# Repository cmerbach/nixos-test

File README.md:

# NixOS

## Quick and dirty setup guide for testing

### Download and run a vm

```sh
# create a tmp folder
mkdir -p tmp

# download the current version of nixos
test ! -f tmp/nixos.iso && wget https://channels.nixos.org/nixos-25.05/latest-nixos-minimal-x86_64-linux.iso -O tmp/nixos.iso || echo "Nothing todo!"

# create the device for install the os
test ! -f tmp/nixos.img && qemu-img create -f raw tmp/nixos.img 100G || echo "Nothing todo!"
```

### Run the vm

> [!NOTE]
> **cpu <CPU> :** Specify a processor architecture to emulate. To see a list of supported architectures, run: `qemu-system-x86_64 -cpu` <br>
> **cpu host :** (Recommended) Emulate the host processor <br>
> **smp <NUMBER> :** Specify the number of cores the guest is permitted to use. The number can be higher than the available cores on the host system. Use `-smp $(nproc)` to use all currently available cores

```sh
# ---( Option A)--- #
# run the boot command with gui
qemu-system-x86_64 -enable-kvm -hda tmp/nixos.img -smp 8 -m 16G -nic user,hostfwd=tcp::8888-:22 -cdrom tmp/nixos.iso -boot d

#---( set a password to root in the vm )--- #
#~$ passwd
```

```sh
# ---( Option B)--- #
# run the boot command just in plain terminal
qemu-system-x86_64 -enable-kvm -hda tmp/nixos.img -smp 8 -m 16G -nic user,hostfwd=tcp::8888-:22 -cdrom tmp/nixos.iso -boot d -nographic -serial mon:stdio

#---( set a password to root in the vm )--- #
#~$ passwd
```

### Login to vm

```sh
ssh-keygen -f "/home/user/.ssh/known_hosts" -R "[127.0.0.1]:8888" && \
sshpass -p '123' \
ssh -o StrictHostKeyChecking=no -o PreferredAuthentications=password nixos@127.0.0.1 -p 8888
```

### Run install

> [!IMPORTANT]  
> The default repo you are using is: **nixos**

> [!CAUTION]
> To run disko needs **2GB** of additional space

#### install by hand

```sh
# set env variables
export ACCOUNT=
export BRANCH=
# run the install 
nix --experimental-features "nix-command flakes" run --refresh --no-write-lock-file git+https://github.com/$ACCOUNT/nixos?ref="$BRANCH"#install
```

#### install by copy and paste

```sh
# set env variables
read -p 'Account: ' ACCOUNT && export ACCOUNT && \
read -p 'REPO: ' REPO && export REPO && \
read -p 'BRANCH: ' BRANCH && export BRANCH && \
read -p 'PASSWORD: ' PASSWORD && export PASSWORD && \
# run the install 
ACCOUNT="$ACCOUNT" PASSWORD="$PASSWORD" nix --experimental-features "nix-command flakes" run --refresh --no-write-lock-file git+https://"$ACCOUNT":"$PASSWORD"@github.com/$ACCOUNT/$REPO?ref="$BRANCH"#install
```

#### install by runme 

```sh
# load env variable
source .env.local
# run the install
ssh-keygen -f "/home/user/.ssh/known_hosts" -R "[127.0.0.1]:8888" && \
sshpass -p '123' \
ssh -t -o StrictHostKeyChecking=no -o PreferredAuthentications=password nixos@127.0.0.1 -p 8888 \
" export REPO='$REPO' && \
export ACCOUNT='$ACCOUNT' && \
export BRANCH='$BRANCH' && \
export PASSWORD='$PASSWORD' && \
ACCOUNT=\"\$ACCOUNT\" PASSWORD=\"\$PASSWORD\" \
nix --experimental-features \"nix-command flakes\" run --refresh --no-write-lock-file git+https://\"\$ACCOUNT\":\"\$PASSWORD\"@github.com/\$ACCOUNT/\$REPO?ref=\"\$BRANCH\"#install"
```

### Reboot and start the system

#### BIOS
```sh
# run in ui remove: -nographic -serial mon:stdio
qemu-system-x86_64 -enable-kvm -hda tmp/nixos.img -smp 8 -m 16G -nic user,hostfwd=tcp::8888-:22 -nographic -serial mon:stdio
```

#### UEFI
```sh
# run in ui remove: -nographic -serial mon:stdio
cp "$(ls /nix/store/*qemu*/share/qemu/edk2-i386-vars.fd | head -1)" /tmp/efi-vars.fd && \
chmod 777 /tmp/efi-vars.fd && \
qemu-system-x86_64 \
  -enable-kvm \
  -machine q35 \
  -cpu host \
  -smp 8 \
  -m 16G \
  -drive if=pflash,format=raw,readonly=on,file="$(ls /nix/store/*qemu*/share/qemu/edk2-x86_64-code.fd | head -1)" \
  -drive if=pflash,format=raw,file=/tmp/efi-vars.fd \
  -drive file=tmp/nixos.img,format=raw \
  -nic user,hostfwd=tcp::8888-:22 \
  -nographic -serial mon:stdio
```

## Arduino

<br>

> [!TIP]
> [Arduino Pro Micro (ATmega32U4)](https://www.amazon.de/EntwicklungBoards-Binghe-Mikrocontroller-Entwicklungsboard-Selbst-USB-Updater/dp/B0D69JLJ97) <br>
> [USB C Adapter](https://www.amazon.de/dp/B0BYK917NM)

---

### Circuit diagram

---

### PCB Design

> [!NOTE]  
> You can go to [JLCPCB](https://jlcpcb.com) and upload the [files](arduino/pcb/touch-shield/production/) and be production ready

---

### Case

---

### Final Product

---

### Code

```sh
# open the arduino ide
arduino-ide
```

> [!IMPORTANT]
>
> - Board Manager -> Arduino AVR Boards -> Install <br>
> - Libary Manager -> Keybaord -> Install <br>
> - Tools -> Board -> Arduino AVR Boards -> Arduino Leonardo <br>
> - Tools -> Port -> /dev/ttyACM0

<br>

A simple script for the USB HID (Human Interface Device) functionality of the Arduino Pro Micro. This code sends a text message whenever the board is connected to a computer.

---

#### Simple example

```cpp
#include <Keyboard.h>

void setup() {
  Keyboard.begin(); // init keyboard
  delay(1000); // wait 2 secounds for the system to be ready
  Keyboard.print(""); // send Text without linebreak
  Keyboard.write(KEY_RETURN); // simulate the Enter key
  Keyboard.end(); // end keyboard
}

void loop() {
  // nothing in the loop, since we only want to send once at startup
}
```

<br>

---

#### Code for Production

> [!CAUTION]
> Think about the keyboard layout! It only works with **us** layout <br>
> Also think about that you are using the us layout when typing! <br>

> [!TIP]
> workaround in my case for GNOME/KDE: <br>
> `gsettings set org.gnome.desktop.input-sources sources "[('xkb', 'us')]"` <br>
> `gsettings set org.gnome.desktop.input-sources sources "[('xkb', 'de')]"` <br>

Upload the [Code](arduino/ino/touch.ino) to the Arduino Pro Micro. Don't forget to update the token for your GitHub account accordingly.

> [!NOTE]  
> `const char* TOKEN = "...";`<br>
> create a GitHub Token, go to: <br>
> Settings -> Developer Settings -> Personal access tokens -> Fine-grained tokens -> REPO -> Repository permissions -> Contents -> read-only -> Generate Token

## Renovate

- [Enabling Renovate for GitHub](https://github.com/apps/renovate)
- [Renovate Dashboard](https://developer.mend.io/github/)

> [!TIP]
> Setting up renovate for specific repos: <br>
> Profile -> Settings -> Integrations -> Applications -> Renovate -> Configure

## Corne Cherry v3 Keyboard

- [Hardware Toolkit](https://keebd.com/de-de/products/corne-cherry-v3-rgb-keyboard-kit)
- [Microcontroller](https://de.aliexpress.com/item/1005006271779544.html)
- [Akko Penguin Switch](https://akkogear.de/products/akko-penguin-switch-silent-45pcs)

> [!TIP]
> Videos for help to build: <br>
> [How To Build A Corne Keyboard: The Complete Beginner's Guide](https://www.youtube.com/watch?v=vzDTdLaAzXc) <br>
> [How to Build a Wireless Corne Keyboard](https://www.youtube.com/watch?v=FJgvi7WShxY) <br>
> [Corne Wireless Split Keyboard Build](https://www.youtube.com/watch?v=Allaz9XloCo) <br>
> [Guide for soldering all components](https://www.youtube.com/watch?v=gA9IZ1u0i2U)

### Build ZMK 

> [!IMPORTANT]
> [Default Values](https://github.com/zmkfirmware/zmk/tree/main/app/boards/shields/corne)

```sh
bash -c "$(curl -fsSL https://zmk.dev/setup.sh)"
# -> 17) Corne -> 10) nice!nano v2 -> Y) Enter -> Y) Enter -> Y) Enter
# rm .github for using local
```

> [!TIP]
> [ZMK System Configuration for Bluetooth and USB](https://zmk.dev/docs/config/system)
> [ZMK Split Configuration](https://zmk.dev/docs/config/split)

#### Custom Build Pipeline

This repository uses a custom GitHub Actions [workflow](.github/workflows/zmk-config.yml) to build ZMK firmware for the Corne Cherry v3 keyboard with Nice!Nano controllers. The pipeline generates two firmware files: `corne_left.uf2` and `corne_right.uf2`.

> [!NOTE]
> Default config is for **bluetooth** connection
> If using `[config:usb]`in the commit message you get the config for usb connection

#### Flashing Process

1. Flash Slave (Left Side) First
- Double-press reset button on Nice!Nano to enter bootloader mode
- Copy the corne_left.uf2 file to the mounted drive
- Wait for automatic disconnect

2. Flash Master (Right Side)
- Double-press reset button on Nice!Nano to enter bootloader mode
- Copy the corne_right.uf2 file to the mounted drive
- Wait for automatic disconnect

3. Connection Sequence
- Power on the master
- Power on the slave via usb or trrs cable
- Slave should automatically connect to master via Bluetooth
- Connect keyboard to computer via Bluetooth (only master will appear in device list)

#### Bluetooth Bond Management

##### Clear Bonds via Config

> [!IMPORTANT]
> - Temporarily enable CONFIG_ZMK_BLE_CLEAR_BONDS_ON_START=y in corne.conf <br>
> - Flash firmware, press reset button once to boot and clear all bonds, then re-comment the line and flash again

##### Clear Bonds via Keymap

> [!CAUTION]
> - **Lower layer + A key: &bt BT_CLR** (clears all stored Bluetooth connections) <br>
> - Use when device won't reconnect after being removed from computer's Bluetooth list <br>
> - This is extremely needed to clear the device for a reconnect

### Keycaps

> [!NOTE] 
> **File:** [keycaps.scad](zmk/keycaps/keycaps.scad)
> If you don't want a socket just set: ```base_platform = false``` <br>
> For a longer keycap simply set the variable: ```wide_keycap = true```
> Labeled keycaps you find in the file: [keycaps-functional.3mf](zmk/keycaps/keycaps-functional.3mf)
> Additionally case: [case.scad](zmk/keycaps/case.scad)

### Layout

> [!TIP]
> [Keymap Editor](https://github.com/nickcoutsos/keymap-editor)
> [Keyboard Layouts](https://neo-layout.org)
> - [Noted](https://dariogoetz.github.io/noted-layout/)
> - [Noted Layout](https://neo-layout.org/Layouts/noted/)

<!-- ## Additional - -->

<!-- Hier könnte Ihre Werbung stehen -->

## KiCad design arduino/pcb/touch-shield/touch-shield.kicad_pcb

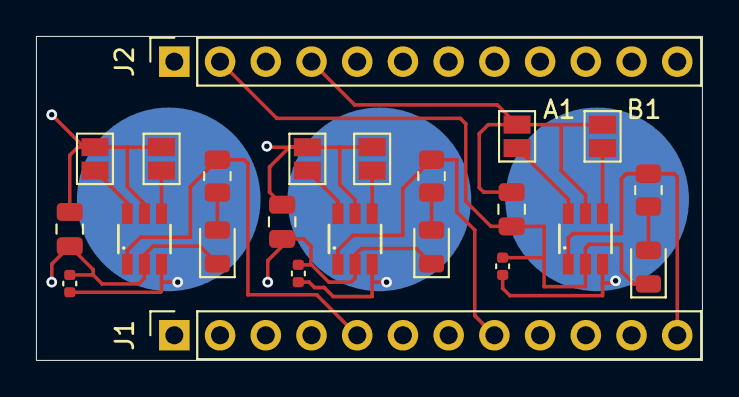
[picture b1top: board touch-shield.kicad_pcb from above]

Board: 4 copper layers, 37.0 x 18.0 mm, 23 parts (0 on the bottom side), 17 nets.

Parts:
A1, A2, A3: SolderJumper_2_Open; SolderJumper-2_P1.3mm_Open_Pad1.0x1.5mm
B1, B2, B3: SolderJumper_2_Open; SolderJumper-2_P1.3mm_Open_Pad1.0x1.5mm
C1, C3, C5: 30pF; C_0402_1005Metric
C2, C4, C6: 1uF; C_0805_2012Metric
D1: LED - Red; LED_0805_2012Metric
D2: LED - Blue; LED_0805_2012Metric
D3: LED - Green; LED_0805_2012Metric
J1: Conn_01x12_Socket_left; PinSocket_1x12_P2.54mm_Vertical
J2: Conn_01x12_Socket_right; PinSocket_1x12_P2.54mm_Vertical
R1, R2, R3: 1K; R_0805_2012Metric
U1, U2, U3: TTP223-BA6

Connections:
/touch-sensor-blue/I/O: J1.5 (8), R2.2, U2.1 (Q)
/touch-sensor-green/I/O: J1.2 (5), R3.2, U3.1 (Q)
/touch-sensor/I/O: J1.9 (12), R1.2, U1.1 (Q)
GND: C1.2, C2.2, C3.2, C4.2, C5.2, C6.2, D1.1 (K), D2.1 (K), D3.1 (K), U1.2 (VSS), U2.2 (VSS), U3.2 (VSS)
unnamed: A1.1 (A), U1.6 (TOG)
unnamed: A2.1 (A), U2.6 (TOG)
unnamed: A3.1 (A), U3.6 (TOG)
unnamed: B1.1 (A), U1.4 (AHLB)
unnamed: B2.1 (A), U2.4 (AHLB)
unnamed: B3.1 (A), U3.4 (AHLB)
unnamed: D1.2 (A), R1.1
unnamed: D2.2 (A), R2.1
unnamed: D3.2 (A), R3.1
unnamed: C1.1, U1.3 (I)
unnamed: C3.1, U2.3 (I)
unnamed: C5.1, U3.3 (I)
VCC: A1.2 (B), A2.2 (B), A3.2 (B), B1.2 (B), B2.2 (B), B3.2 (B), C2.1, C4.1, C6.1, U1.5 (VDD), U2.5 (VDD), U3.5 (VDD)

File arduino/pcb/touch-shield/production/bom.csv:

"Reference","Value","Datasheet","Footprint","Qty","DNP","JLCPCB","Manufacturer Part"
"C1,C3,C5","30pF","~","Capacitor_SMD:C_0402_1005Metric","3","","C1570","0402CG300J500NT"
"C2,C4,C6","1uF","~","Capacitor_SMD:C_0805_2012Metric","3","","C35795","0805F105M500NT"
"D1","LED - Red","~","LED_SMD:LED_0805_2012Metric","1","","C84256","NCD0805R1"
"D2","LED - Blue","~","LED_SMD:LED_0805_2012Metric","1","","C7429915","NCD0603B5"
"D3","LED - Green","~","LED_SMD:LED_0805_2012Metric","1","","C7429914","NCD0603G3"
"J1","Conn_01x12_Socket_left","~","Connector_PinSocket_2.54mm:PinSocket_1x12_P2.54mm_Vertical","1","","C5224029","PM2.54-1*12"
"J2","Conn_01x12_Socket_right","~","Connector_PinSocket_2.54mm:PinSocket_1x12_P2.54mm_Vertical","1","","C5224029","PM2.54-1*12"
"R1,R2,R3","1K","~","Resistor_SMD:R_0805_2012Metric","3","","C17513","0805W8F1001T5E"
"U1,U2,U3","TTP223-BA6","","extra:TTP223-BA6","3","","C2890349","TTP233H-BA6"

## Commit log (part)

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2025-05-23 docs(Readme): init commit
2025-05-23 docs(Readme): how to run and start a nixos vm
2025-05-24 feat(arduino): create pcb touch sensor with kicad
2025-05-24 docs(Readme): add pictures to the documentation of pcb design
2025-05-24 feat(arduino): add 3d design via openscad for case
2025-05-24 docs(Readme): add pictures to the documentation for the 3d case design
2025-05-24 docs(Readme): add pictures to the documentation for the final product
2025-05-24 refactor(Readme): add additional pictures to the documentation
2025-05-24 feat(arduino): add script for download a private repository from github
2025-05-25 test(toplevel): test of a working btrfs system
2025-05-25 test(toplevel): make a non pass version
2025-05-25 test(toplevel): dont ask for root password
2025-05-25 test(toplevel): other approce for non root
2025-05-25 test(toplevel): make run the vm in cli
2025-05-25 test(toplevel): test without a boot.nix
2025-05-25 test(toplevel): test desktop.nix
2025-05-30 test(version): test new package version 25.05
2025-05-30 fix(pkgs): package error v4l2loopback
2025-07-14 test(toplevel): run vm in cli
2025-07-14 docs(Readme): make install command independent of the repo name
2025-07-14 feat(renovate): add renovate config for zmk
2025-07-14 feat(renovate): add renovate config for zephyr
2025-07-14 feat(renovate): add basic renovate config
2025-07-14 feat(renovate): add renovate config for nixos, pkgs, home
2025-07-14 docs(Readme): add steps for how to enable renovate for repo
2025-07-14 chore(config): migrate config .github/renovate.json
2025-07-14 feat(renovate): disable dependency dashboard
2025-07-15 feat(zmk): create openscad file for keycaps
2025-07-15 feat(zmk): basic customize the zmk config
2025-07-15 feat(zmk): create and add a basic zmk config for nice!nano
2025-07-15 build(zmk): create workflow for zmk build logic
2025-07-19 test(zmk): test usb and bluetooth connection
2025-07-19 play arround with the config [config:usb]
2025-07-19 docs(README): update the Readme.md for the process of customize corne keyboard
2025-07-19 feat(zmk): setting up a new keyboard layout
2025-07-19 refactor(zmk): use main branch form zmk in workflow
2025-07-19 fix(workflows/zmk): fix path for zmk artifacs
2025-07-19 fix(workflows/zmk): downgrade the zephyr version
2025-07-26 test(workflows/zmk): add optional flag in commit msg [config:usb]
2025-07-26 feat(zmk): enable oled display
2025-08-11 refactor(zmk): change to neo2 keyboard layout
2025-08-11 refactor(zmk): change to noted keyboard layout
2025-08-11 feat(zmk): setting up layer 2 for programming chars
2025-08-11 refactor(zmk): add and change some settings for power management config
2025-08-17 test(refactor): update from 24.11 to 25.05 and split desktop settings
2025-08-17 test(hyprland): setup a basic config
2025-08-17 test(refactor): files new syle try if i can put gnome settings from home in gnome
2025-08-17 test(refactor-feat): try gnome settings as module in homemanager for enable
2025-08-17 test(add-feat): add all pkgs and try if they get installed
2025-08-17 test(hyprland): add settings for hyprland and testing
2025-08-18 test(hyprland): try a new style and config
2025-09-14 chore(deps): update zmk to v0.3.0
2025-09-14 chore(deps): update actions/checkout action to v5
2025-10-14 chore(deps): update zephyr to v0.17.4
2025-10-22 feat(rp2040): first basic working setup
2025-10-22 feat(rp2040): first proof of concept for a menu - working
2025-10-22 feat(rp2040/menu): create circles and rectangles in menu
2025-11-30 chore(deps): update actions/checkout action to v6
2025-12-22 feat(rp2040/menu): add swipe option back to main menu
2025-12-22 test(zmk): change tab and shift
2026-02-26 chore(deps): update actions/upload-artifact action to v7
2026-03-25 chore(deps): update zephyr to v1
2026-05-30 chore(deps): update nixos to v26
